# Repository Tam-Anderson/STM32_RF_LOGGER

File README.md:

# STM32_RF_LOGGER
 simple stm 32 RF logger PCB design 
 See updates in Rev2 branch

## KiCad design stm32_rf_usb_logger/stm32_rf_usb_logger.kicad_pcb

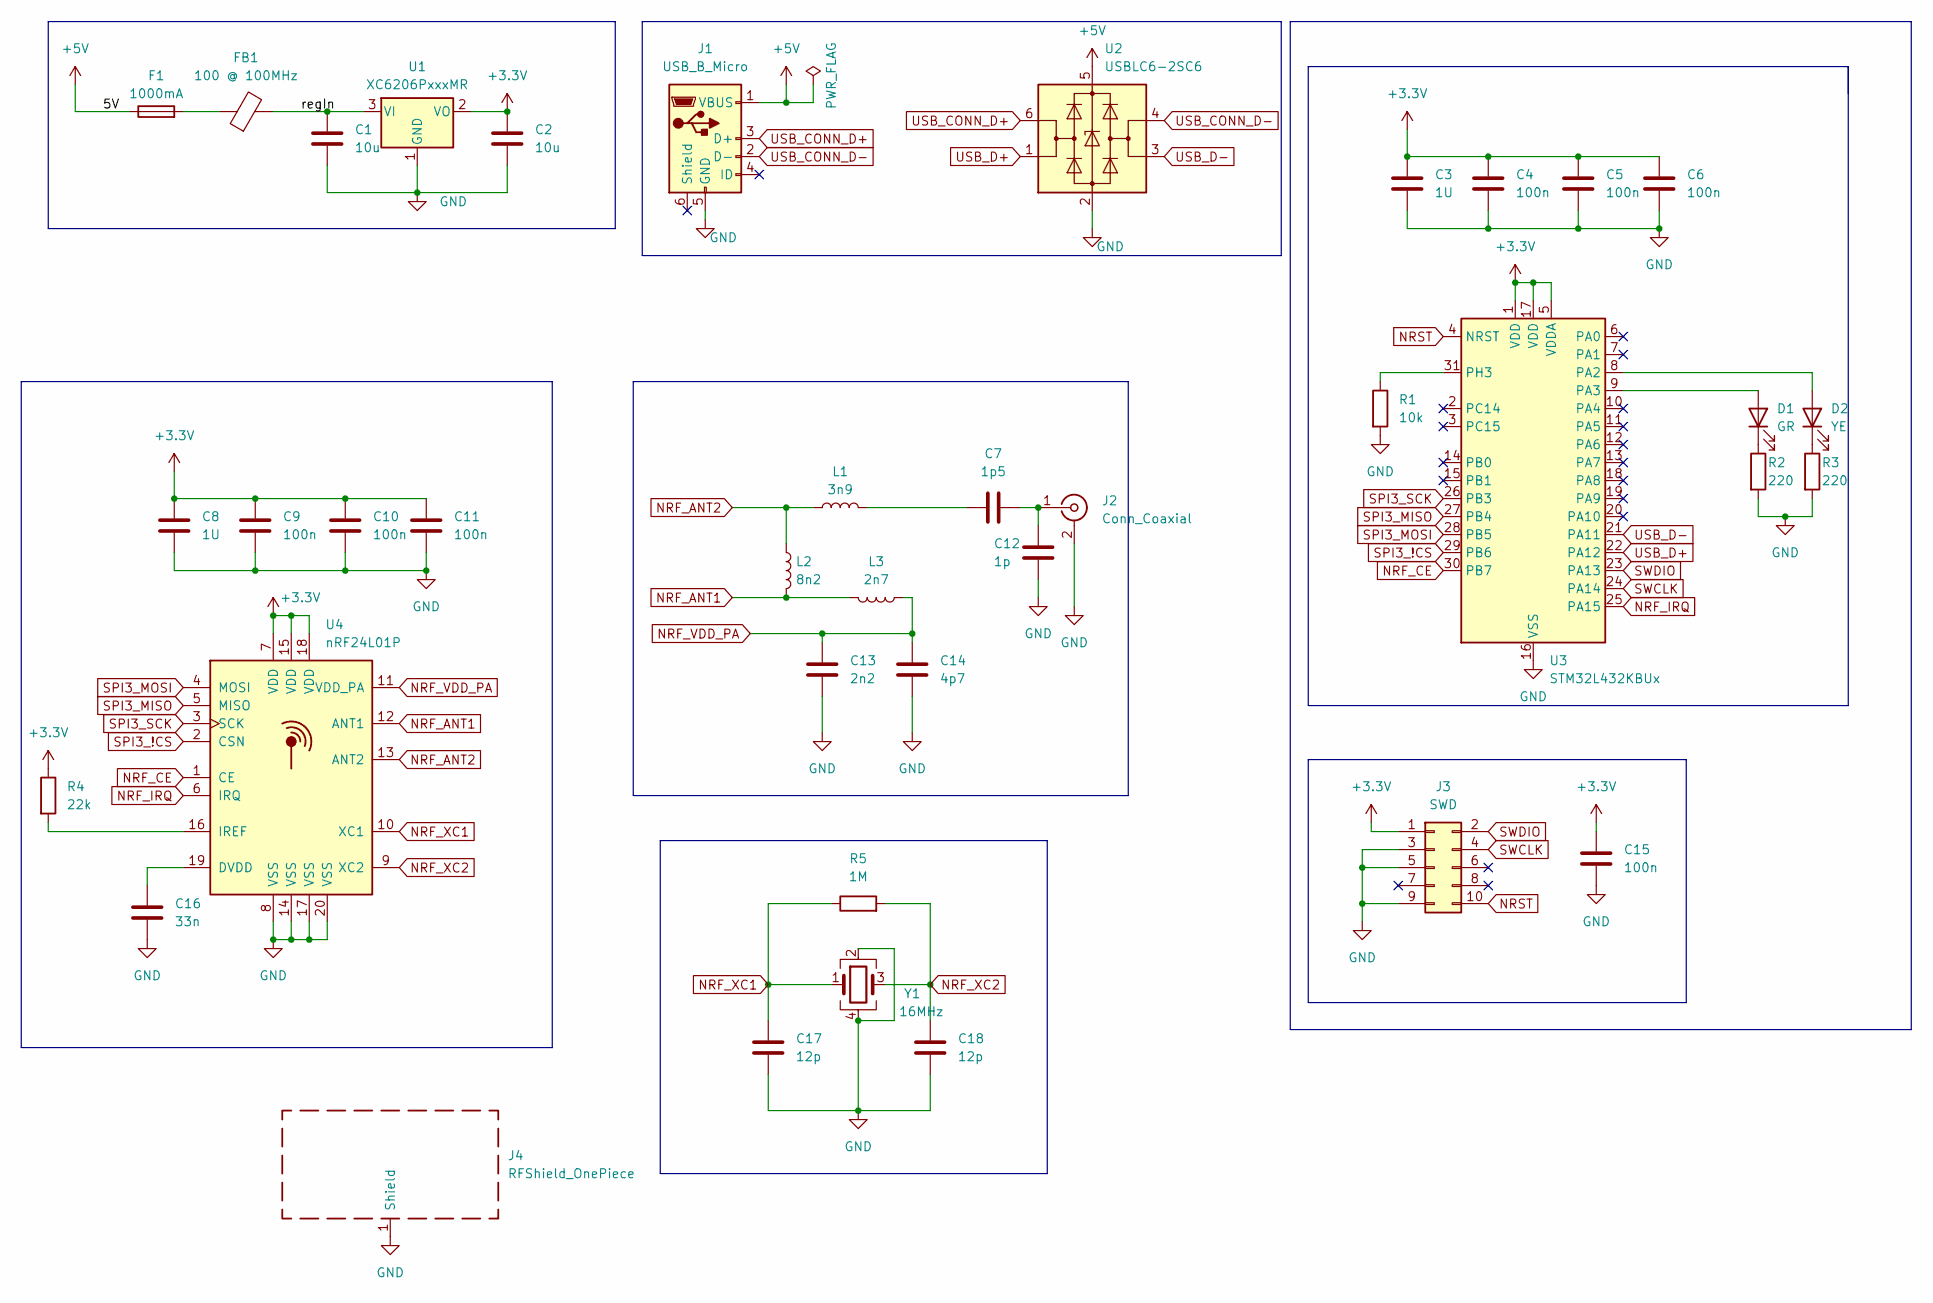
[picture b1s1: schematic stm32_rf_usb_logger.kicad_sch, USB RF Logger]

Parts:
C1, C2: 10u; C_0603_1608Metric_Pad1.08x0.95mm_HandSolder
C3, C8: 1U; C_0402_1005Metric
C4, C5, C6, C9, C10, C11, C15: 100n; C_0402_1005Metric
C7: 1p5; C_0402_1005Metric
C12: 1p; C_0402_1005Metric
C13: 2n2; C_0402_1005Metric
C14: 4p7; C_0402_1005Metric
C16: 33n; C_0402_1005Metric
C17, C18: 12p; C_0402_1005Metric
D1: GR; LED_0402_1005Metric
D2: YE; LED_0402_1005Metric
F1: 1000mA; Fuse_0603_1608Metric_Pad1.05x0.95mm_HandSolder
FB1: 100 @ 100MHz; L_0805_2012Metric
J1: USB_B_Micro; USB_Micro-B_Molex-105017-0001
J2: Conn_Coaxial; SMA_Samtec_SMA-J-P-X-ST-EM1_EdgeMount
J3: SWD; PinHeader_2x05_P2.54mm_Vertical
J4: RFShield_OnePiece; Laird_Technologies_BMI-S-102_16.50x16.50mm
L1: 3n9; L_0402_1005Metric
L2: 8n2; L_0402_1005Metric
L3: 2n7; L_0402_1005Metric
R1: 10k; R_0402_1005Metric
R2, R3: 220; R_0603_1608Metric
R4: 22k; R_0603_1608Metric
R5: 1M; R_0402_1005Metric_Pad0.72x0.64mm_HandSolder
U1: XC6206PxxxMR; SOT-23-3
U2: USBLC6-2SC6; SOT-23-6
U3: STM32L432KBUx; QFN-32-1EP_5x5mm_P0.5mm_EP3.45x3.45mm
U4: nRF24L01P; QFN-20-1EP_4x4mm_P0.5mm_EP2.5x2.5mm
Y1: 16MHz; Crystal_SMD_3225-4Pin_3.2x2.5mm

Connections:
+3.3V: C2.1, C3.1, C4.1, C5.1, C6.1, C8.1, C9.1, C10.1, C11.1, C15.1, J3.1, R4.1, U1.2 (VO), U3.1 (VDD), U3.5 (VDDA), U3.17 (VDD), U4.7 (VDD), U4.15 (VDD), U4.18 (VDD)
+5V: F1.1, J1.1 (VBUS), U2.5 (VBUS)
/regIn: C1.1, FB1.2, U1.3 (VI)
GND: C1.2, C2.2, C3.2, C4.2, C5.2, C6.2, C8.2, C9.2, C10.2, C11.2, C12.2, C13.1, C14.1, C15.2, C16.2, C17.2, C18.2, J1.5 (GND), J2.2 (Ext), J3.3, J3.5, J3.9, J4.1, R1.2, R2.2, R3.2, U1.1 (GND), U2.2 (GND), U3.16 (VSS), U3.32 (VSS), U3.33 (VSS), U4.8 (VSS), U4.14 (VSS), U4.17 (VSS), U4.20 (VSS), Y1.2, Y1.4; also elsewhere on the board
NRF_ANT1: L2.2, L3.2, U4.12 (ANT1)
NRF_ANT2: L1.1, L2.1, U4.13 (ANT2)
NRF_CE: U3.30 (PB7), U4.1 (CE)
NRF_IRQ: U3.25 (PA15), U4.6 (IRQ)
NRF_VDD_PA: C13.2, C14.2, L3.1, U4.11 (VDD_PA)
NRF_XC1: C17.1, R5.1, U4.10 (XC1), Y1.1
NRF_XC2: C18.1, R5.2, U4.9 (XC2), Y1.3
NRST: J3.10, U3.4 (NRST)
unnamed: C7.1, L1.2
unnamed: D1.2 (A), U3.9 (PA3)
unnamed: D1.1 (K), R2.1
unnamed: D2.2 (A), U3.8 (PA2)
unnamed: D2.1 (K), R3.1
unnamed: F1.2, FB1.1
unnamed: C7.2, C12.1, J2.1 (In)
unnamed: R1.1, U3.31 (PH3)
unnamed: C16.1, U4.19 (DVDD)
unnamed: R4.2, U4.16 (IREF)
SPI3_!CS: U3.29 (PB6), U4.2 (CSN)
SPI3_MISO: U3.27 (PB4), U4.5 (MISO)
SPI3_MOSI: U3.28 (PB5), U4.4 (MOSI)
SPI3_SCK: U3.26 (PB3), U4.3 (SCK)
SWCLK: J3.4, U3.24 (PA14)
SWDIO: J3.2, U3.23 (PA13)
USB_CONN_D+: J1.3 (D+), U2.6 (I/O1)
USB_CONN_D-: J1.2 (D-), U2.4 (I/O2)
USB_D+: U2.1 (I/O1), U3.22 (PA12)
USB_D-: U2.3 (I/O2), U3.21 (PA11)

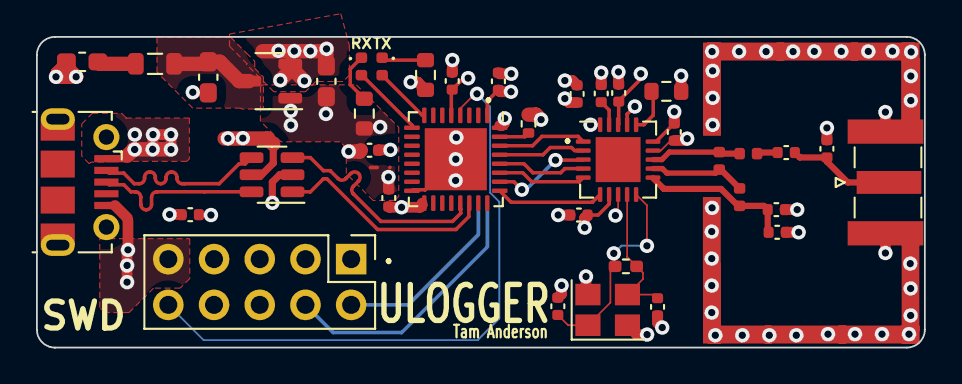
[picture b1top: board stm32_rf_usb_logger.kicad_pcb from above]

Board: 4 copper layers, 49.3 x 17.3 mm, 39 parts (0 on the bottom side), 32 nets.

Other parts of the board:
e: RFShield_OnePiece; Laird_Technologies_BMI-S-102_16.50x16.50mm

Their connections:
GND: e.1 (Shield); also elsewhere on the board

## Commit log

2023-08-09 schematics updates
    added schematic power, usb, ucontroller and nrf
2023-08-11 completed layout
    Layout completed . However, minor changes have to be made regarding fills and pours.
2023-08-11 test commit
    added random line
2023-08-11 deleted layout for testing
2023-08-11 KiCAD auto
2023-08-11 completed layout
2023-08-12 Done
2023-08-13 optimised grounding
    moved vias closer to pads
2023-08-13 kicad_Auto
